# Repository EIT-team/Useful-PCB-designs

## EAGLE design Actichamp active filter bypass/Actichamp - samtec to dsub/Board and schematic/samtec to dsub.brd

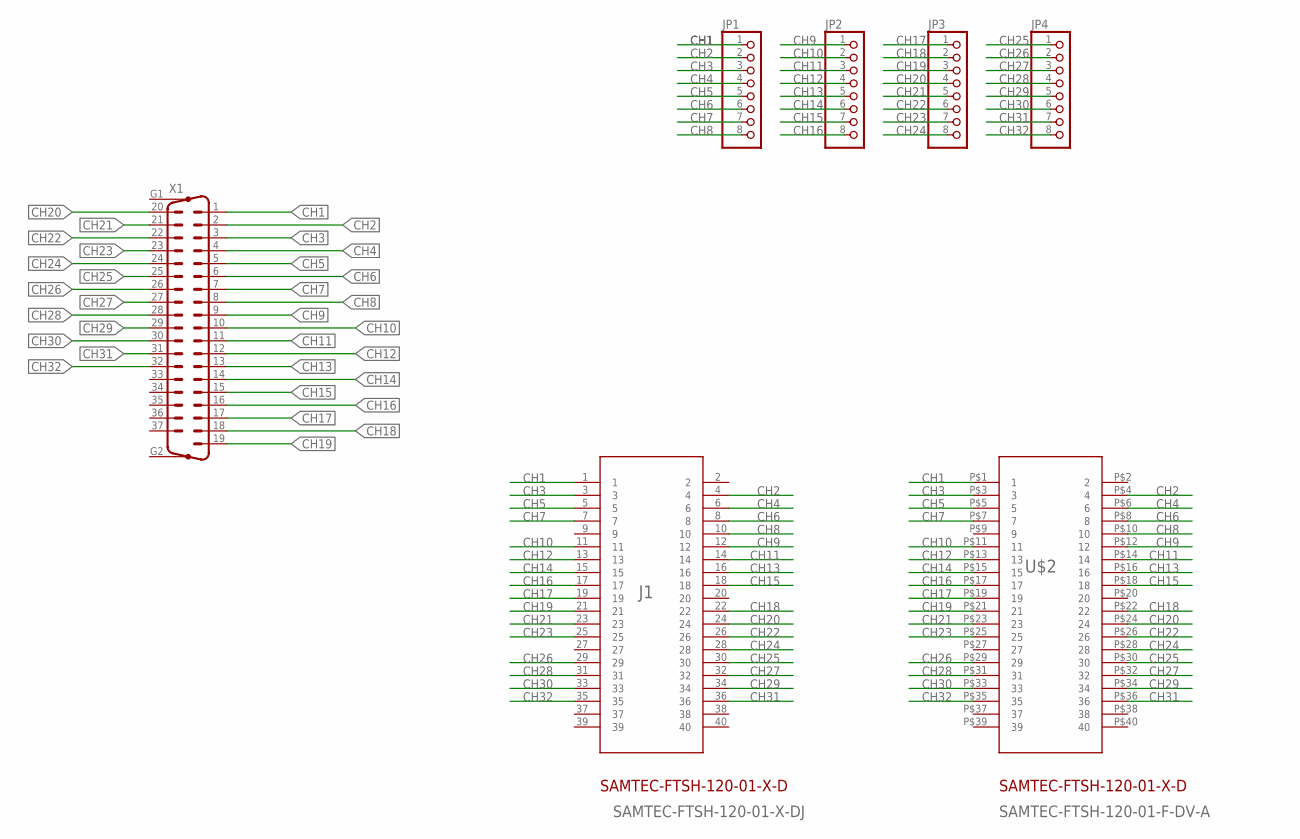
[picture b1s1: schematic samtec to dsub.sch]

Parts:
J1: SAMTEC-FTSH-120-01-X-DJ; SAMTEC-FTSH-120-01-X-D
JP1, JP2, JP3, JP4: PINHD-1X8; 1X08
U$2: SAMTEC-FTSH-120-01-F-DV-A; SAMTEC-FTSH-LARGEPAD
X1: M37HP

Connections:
CH1: J1.1, JP1.1, U$2.P$1 (1), X1.1
CH2: J1.4, JP1.2, U$2.P$4 (4), X1.2
CH3: J1.3, JP1.3, U$2.P$3 (3), X1.3
CH4: J1.6, JP1.4, U$2.P$6 (6), X1.4
CH5: J1.5, JP1.5, U$2.P$5 (5), X1.5
CH6: J1.8, JP1.6, U$2.P$8 (8), X1.6
CH7: J1.7, JP1.7, U$2.P$7 (7), X1.7
CH8: J1.10, JP1.8, U$2.P$10 (10), X1.8
CH9: J1.12, JP2.1, U$2.P$12 (12), X1.9
CH10: J1.11, JP2.2, U$2.P$11 (11), X1.10
CH11: J1.14, JP2.3, U$2.P$14 (14), X1.11
CH12: J1.13, JP2.4, U$2.P$13 (13), X1.12
CH13: J1.16, JP2.5, U$2.P$16 (16), X1.13
CH14: J1.15, JP2.6, U$2.P$15 (15), X1.14
CH15: J1.18, JP2.7, U$2.P$18 (18), X1.15
CH16: J1.17, JP2.8, U$2.P$17 (17), X1.16
CH17: J1.19, JP3.1, U$2.P$19 (19), X1.17
CH18: J1.22, JP3.2, U$2.P$22 (22), X1.18
CH19: J1.21, JP3.3, U$2.P$21 (21), X1.19
CH20: J1.24, JP3.4, U$2.P$24 (24), X1.20
CH21: J1.23, JP3.5, U$2.P$23 (23), X1.21
CH22: J1.26, JP3.6, U$2.P$26 (26), X1.22
CH23: J1.25, JP3.7, U$2.P$25 (25), X1.23
CH24: J1.28, JP3.8, U$2.P$28 (28), X1.24
CH25: J1.30, JP4.1, U$2.P$30 (30), X1.25
CH26: J1.29, JP4.2, U$2.P$29 (29), X1.26
CH27: J1.32, JP4.3, U$2.P$32 (32), X1.27
CH28: J1.31, JP4.4, U$2.P$31 (31), X1.28
CH29: J1.34, JP4.5, U$2.P$34 (34), X1.29
CH30: J1.33, JP4.6, U$2.P$33 (33), X1.30
CH31: J1.36, JP4.7, U$2.P$36 (36), X1.31
CH32: J1.35, JP4.8, U$2.P$35 (35), X1.32

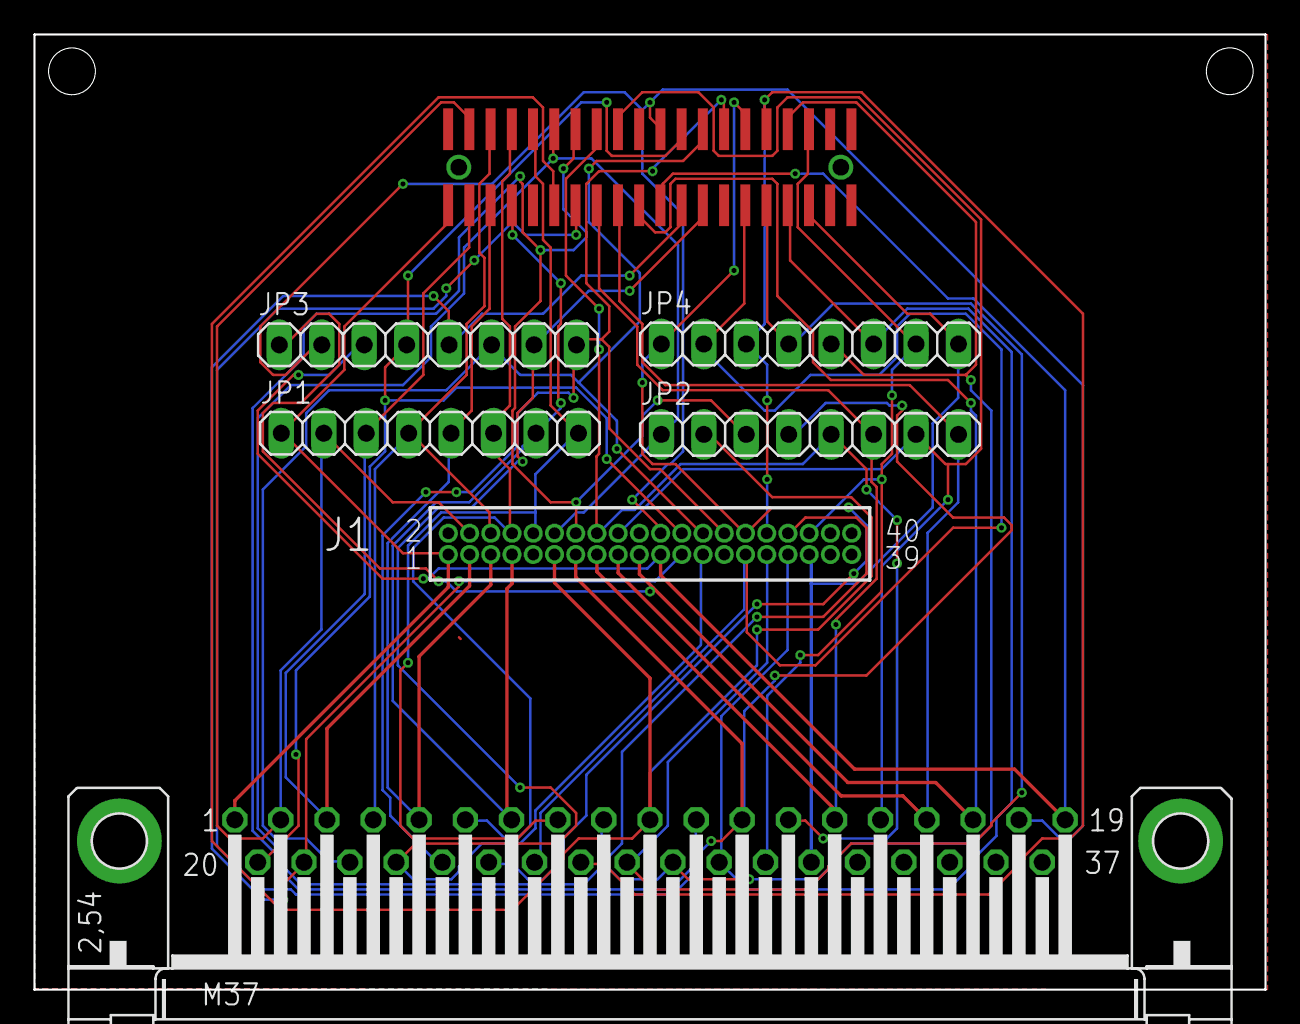
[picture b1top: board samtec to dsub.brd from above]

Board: 2 copper layers, 73.7 x 57.1 mm, 7 parts (0 on the bottom side), 32 nets.

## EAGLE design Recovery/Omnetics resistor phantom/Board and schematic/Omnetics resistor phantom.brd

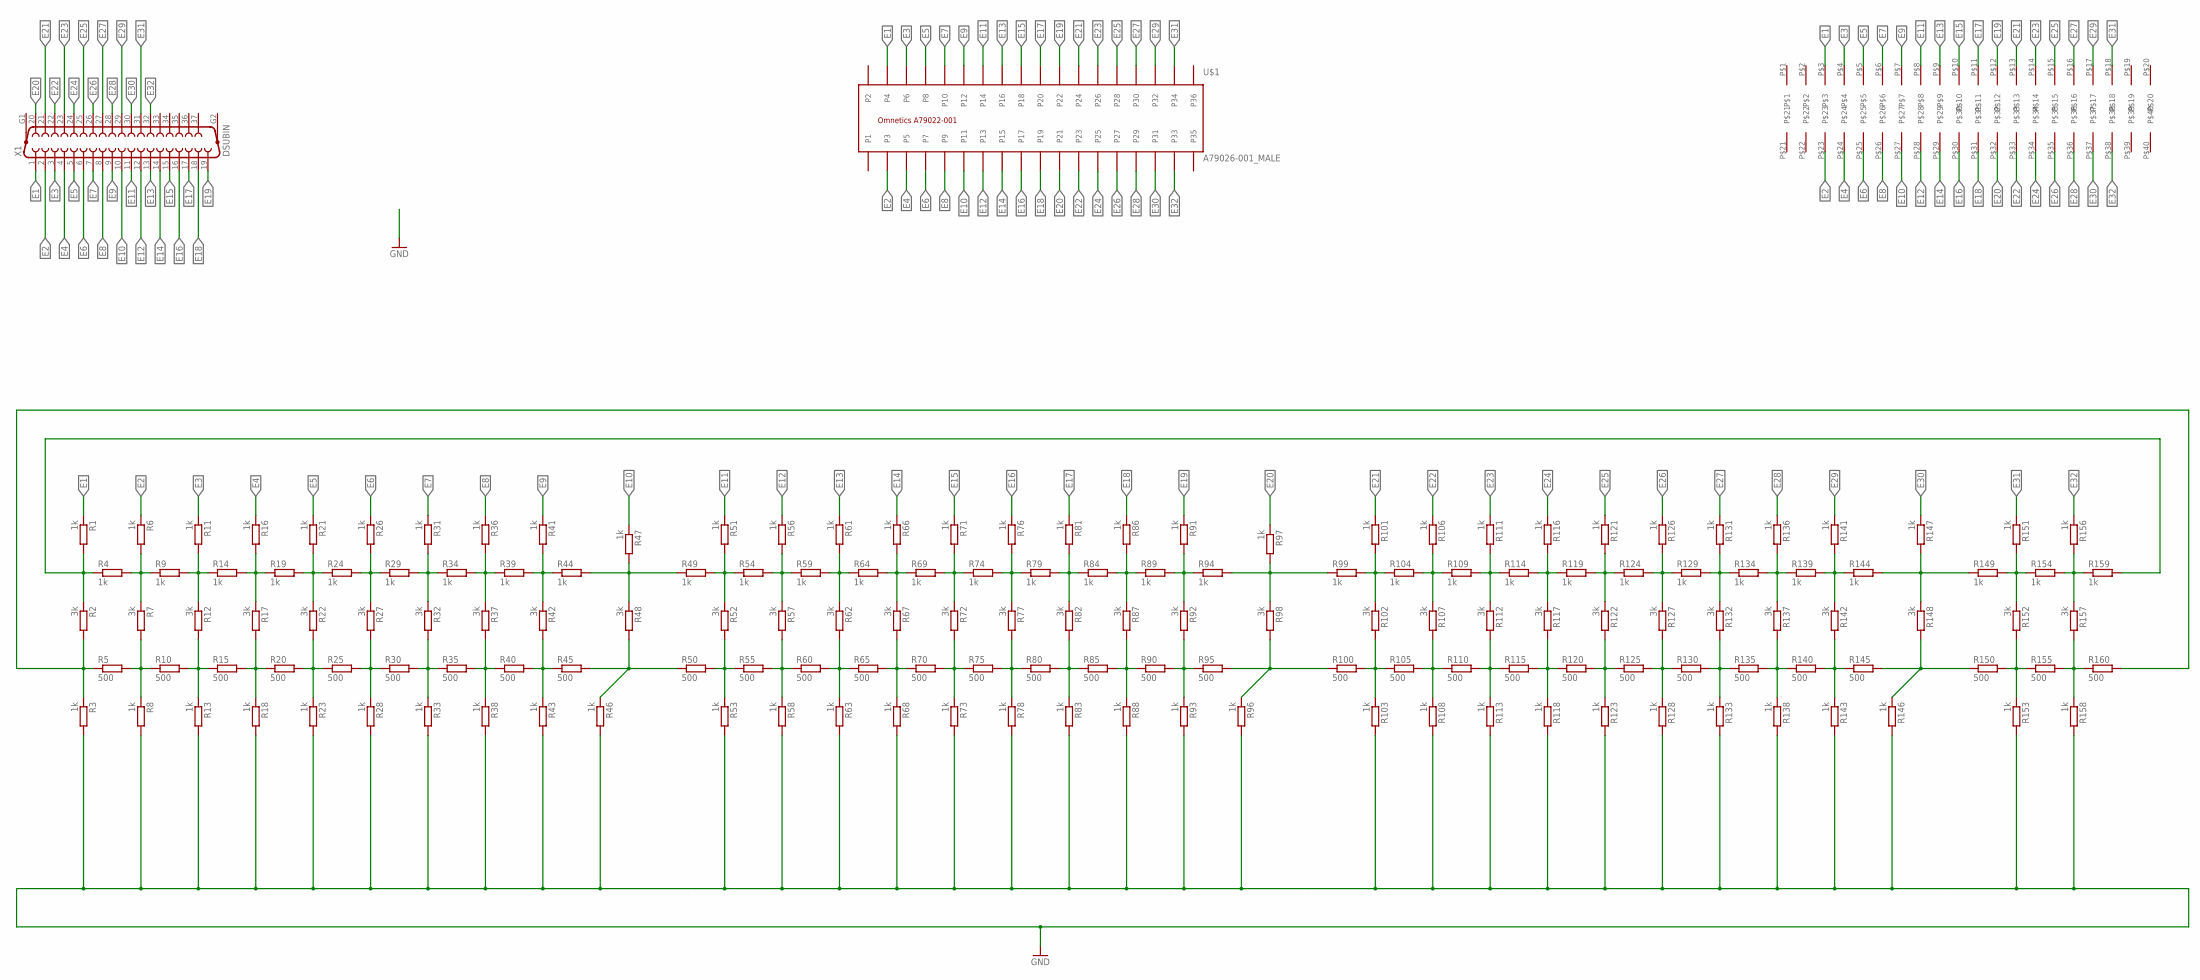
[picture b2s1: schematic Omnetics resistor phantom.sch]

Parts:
R1, R3, R4, R6, R8, R9, R11, R13, R14, R16, R18, R19, R21, R23, R24, R26, R28, R29, R31, R33, R34, R36, R38, R39, R41, R43, R44, R46, R47, R49, R51, R53, R54, R56, R58, R59, R61, R63, R64, R66, R68, R69, R71, R73, R74, R76, R78, R79, R81, R83, R84, R86, R88, R89, R91, R93, R94, R96, R97, R99, R101, R103, R104, R106, R108, R109, R111, R113, R114, R116, R118, R119, R121, R123, R124, R126, R128, R129, R131, R133, R134, R136, R138, R139, R141, R143, R144, R146, R147, R149, R151, R153, R154, R156, R158, R159: 1k; R0402
R2, R7, R12, R17, R22, R27, R32, R37, R42, R48, R52, R57, R62, R67, R72, R77, R82, R87, R92, R98, R102, R107, R112, R117, R122, R127, R132, R137, R142, R148, R152, R157: 3k; R0402
R5, R10, R15, R20, R25, R30, R35, R40, R45, R50, R55, R60, R65, R70, R75, R80, R85, R90, R95, R100, R105, R110, R115, R120, R125, R130, R135, R140, R145, R150, R155, R160: 500; R0402
U$1: A79026-001_MALE
U$2: SAMTEC_FTSH_LARGEPAD; SAMTEC-FTSH-LARGEPAD
X1: DSUBIN; F37VP

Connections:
E1: R1.1, U$1.P4, U$2.P$3, X1.1
E2: R6.1, U$1.P3, U$2.P$23, X1.2
E3: R11.1, U$1.P6, U$2.P$4, X1.3
E4: R16.1, U$1.P5, U$2.P$24, X1.4
E5: R21.1, U$1.P8, U$2.P$5, X1.5
E6: R26.1, U$1.P7, U$2.P$25, X1.6
E7: R31.1, U$1.P10, U$2.P$6, X1.7
E8: R36.1, U$1.P9, U$2.P$26, X1.8
E9: R41.1, U$1.P12, U$2.P$7, X1.9
E10: R47.1, U$1.P11, U$2.P$27, X1.10
E11: R51.1, U$1.P14, U$2.P$8, X1.11
E12: R56.1, U$1.P13, U$2.P$28, X1.12
E13: R61.1, U$1.P16, U$2.P$9, X1.13
E14: R66.1, U$1.P15, U$2.P$29, X1.14
E15: R71.1, U$1.P18, U$2.P$10, X1.15
E16: R76.1, U$1.P17, U$2.P$30, X1.16
E17: R81.1, U$1.P20, U$2.P$11, X1.17
E18: R86.1, U$1.P19, U$2.P$31, X1.18
E19: R91.1, U$1.P22, U$2.P$12, X1.19
E20: R97.1, U$1.P21, U$2.P$32, X1.20
E21: R101.1, U$1.P24, U$2.P$13, X1.21
E22: R106.1, U$1.P23, U$2.P$33, X1.22
E23: R111.1, U$1.P26, U$2.P$14, X1.23
E24: R116.1, U$1.P25, U$2.P$34, X1.24
E25: R121.1, U$1.P28, U$2.P$15, X1.25
E26: R126.1, U$1.P27, U$2.P$35, X1.26
E27: R131.1, U$1.P30, U$2.P$16, X1.27
E28: R136.1, U$1.P29, U$2.P$36, X1.28
E29: R141.1, U$1.P32, U$2.P$17, X1.29
E30: R147.1, U$1.P31, U$2.P$37, X1.30
E31: R151.1, U$1.P34, U$2.P$18, X1.31
E32: R156.1, U$1.P33, U$2.P$38, X1.32
E38: R1.2, R2.1, R4.1, R159.2
E39: R4.2, R6.2, R7.1, R9.1
E40: R9.2, R11.2, R12.1, R14.1
E41: R14.2, R16.2, R17.1, R19.1
E42: R19.2, R21.2, R22.1, R24.1
E43: R24.2, R26.2, R27.1, R29.1
E44: R29.2, R31.2, R32.1, R34.1
E45: R34.2, R36.2, R37.1, R39.1
E46: R39.2, R41.2, R42.1, R44.1
E47: R44.2, R47.2, R48.1, R49.1
E48: R49.2, R51.2, R52.1, R54.1
E49: R54.2, R56.2, R57.1, R59.1
E50: R59.2, R61.2, R62.1, R64.1
E51: R64.2, R66.2, R67.1, R69.1
E52: R69.2, R71.2, R72.1, R74.1
E53: R74.2, R76.2, R77.1, R79.1
E54: R79.2, R81.2, R82.1, R84.1
E55: R84.2, R86.2, R87.1, R89.1
E56: R89.2, R91.2, R92.1, R94.1
E57: R94.2, R97.2, R98.1, R99.1
E58: R99.2, R101.2, R102.1, R104.1
E59: R104.2, R106.2, R107.1, R109.1
E60: R109.2, R111.2, R112.1, R114.1
E61: R114.2, R116.2, R117.1, R119.1
E63: R124.2, R126.2, R127.1, R129.1
E64: R129.2, R131.2, R132.1, R134.1
E65: R134.2, R136.2, R137.1, R139.1
E66: R139.2, R141.2, R142.1, R144.1
E67: R144.2, R147.2, R148.1, R149.1
E68: R149.2, R151.2, R152.1, R154.1
E69: R154.2, R156.2, R157.1, R159.1
GND: R3.2, R8.2, R13.2, R18.2, R23.2, R28.2, R33.2, R38.2, R43.2, R46.2, R53.2, R58.2, R63.2, R68.2, R73.2, R78.2, R83.2, R88.2, R93.2, R96.2, R103.2, R108.2, R113.2, R118.2, R123.2, R128.2, R133.2, R138.2, R143.2, R146.2, R153.2, R158.2
unnamed: R119.2, R121.2, R122.1, R124.1
unnamed: R2.2, R3.1, R5.1, R160.2
unnamed: R5.2, R7.2, R8.1, R10.1
unnamed: R10.2, R12.2, R13.1, R15.1
unnamed: R15.2, R17.2, R18.1, R20.1
unnamed: R20.2, R22.2, R23.1, R25.1
unnamed: R25.2, R27.2, R28.1, R30.1
unnamed: R30.2, R32.2, R33.1, R35.1
unnamed: R35.2, R37.2, R38.1, R40.1
unnamed: R40.2, R42.2, R43.1, R45.1
unnamed: R50.2, R52.2, R53.1, R55.1
unnamed: R55.2, R57.2, R58.1, R60.1
unnamed: R60.2, R62.2, R63.1, R65.1
unnamed: R65.2, R67.2, R68.1, R70.1
unnamed: R70.2, R72.2, R73.1, R75.1
unnamed: R75.2, R77.2, R78.1, R80.1
unnamed: R80.2, R82.2, R83.1, R85.1
unnamed: R85.2, R87.2, R88.1, R90.1
unnamed: R90.2, R92.2, R93.1, R95.1
unnamed: R100.2, R102.2, R103.1, R105.1
unnamed: R105.2, R107.2, R108.1, R110.1
unnamed: R110.2, R112.2, R113.1, R115.1
unnamed: R115.2, R117.2, R118.1, R120.1
unnamed: R120.2, R122.2, R123.1, R125.1
unnamed: R125.2, R127.2, R128.1, R130.1
unnamed: R130.2, R132.2, R133.1, R135.1
unnamed: R135.2, R137.2, R138.1, R140.1
unnamed: R140.2, R142.2, R143.1, R145.1
unnamed: R150.2, R152.2, R153.1, R155.1
unnamed: R155.2, R157.2, R158.1, R160.1
SW_IN1: R45.2, R46.1, R48.2, R50.1
SW_IN2: R95.2, R96.1, R98.2, R100.1
SW_IN3: R145.2, R146.1, R148.2, R150.1

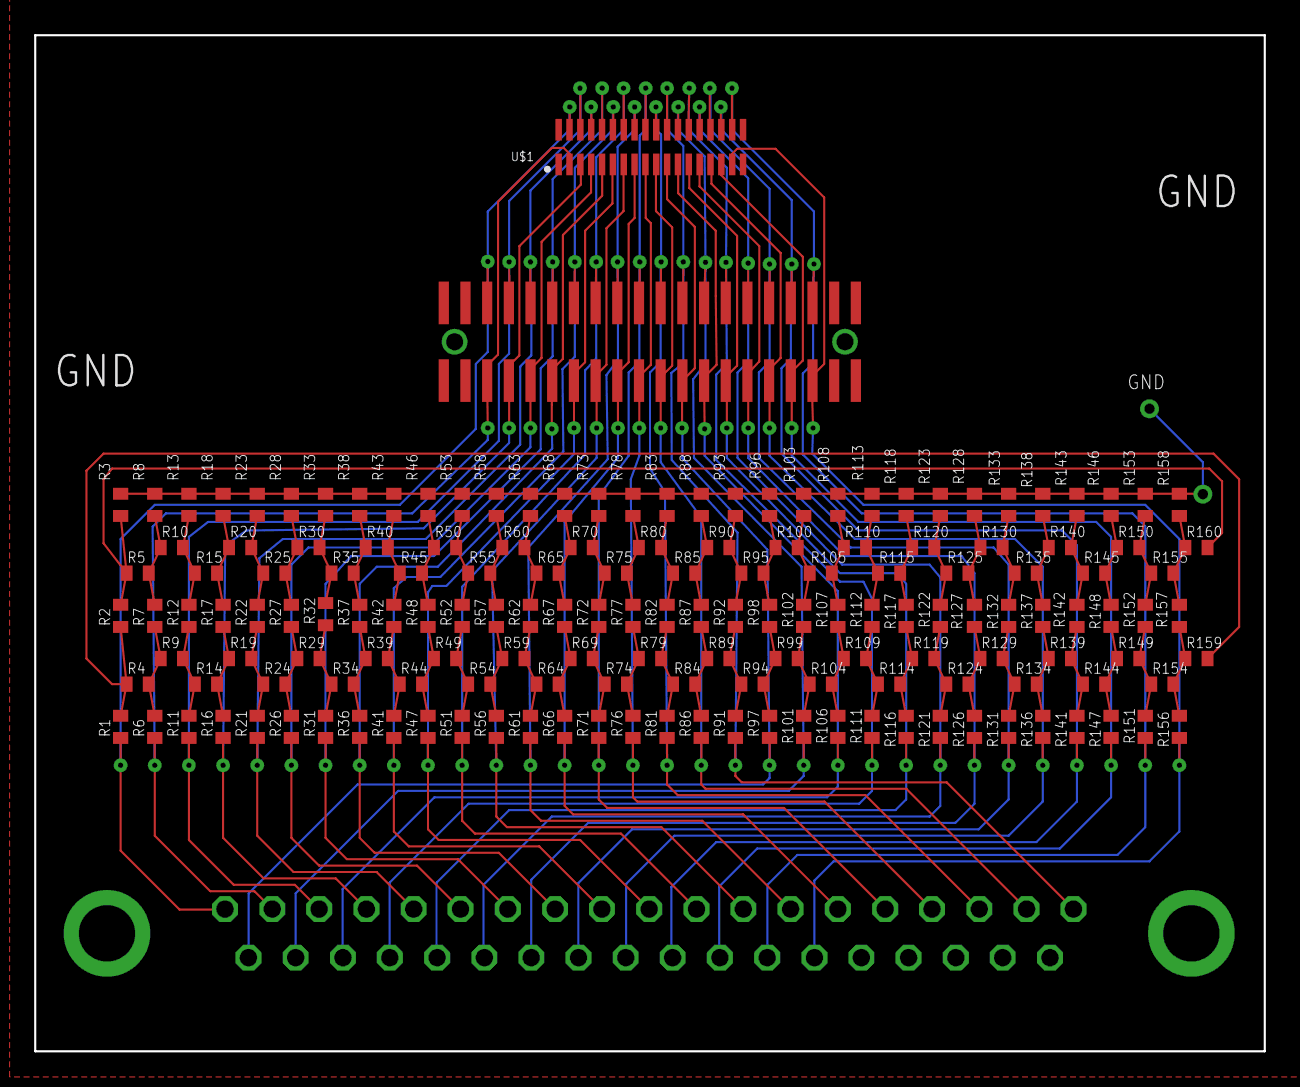
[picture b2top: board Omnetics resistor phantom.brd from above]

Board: 2 copper layers, 72.0 x 59.5 mm, 163 parts (1 on the bottom side), 97 nets.

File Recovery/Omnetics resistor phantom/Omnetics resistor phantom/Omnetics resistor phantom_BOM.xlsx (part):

Part | Value | Device | Package | Description | MPN | OC_FARNELL | PCBTRAINFREE
R1 | 1k | R-EU_R0402 | R0402 | RESISTOR, European symbol | MC00625W040211K | 1358043 | PCBTRAINFREESTOCK
R2 | 3k | R-EU_R0402 | R0402 | RESISTOR, European symbol | MC00625W040213K | 2130389 | PCBTRAINFREESTOCK
R3 | 1k | R-EU_R0402 | R0402 | RESISTOR, European symbol | MC00625W040211K | 1358043 | PCBTRAINFREESTOCK
R4 | 1k | R-EU_R0402 | R0402 | RESISTOR, European symbol | MC00625W040211K | 1358043 | PCBTRAINFREESTOCK
R5 | 500 | R-EU_R0402 | R0402 | RESISTOR, European symbol | MC00625W04021510R | 2130329 | PCBTRAINFREESTOCK
R6 | 1k | R-EU_R0402 | R0402 | RESISTOR, European symbol | MC00625W040211K | 1358043 | PCBTRAINFREESTOCK
R7 | 3k | R-EU_R0402 | R0402 | RESISTOR, European symbol | MC00625W040213K | 2130389 | PCBTRAINFREESTOCK
R8 | 1k | R-EU_R0402 | R0402 | RESISTOR, European symbol | MC00625W040211K | 1358043 | PCBTRAINFREESTOCK
R9 | 1k | R-EU_R0402 | R0402 | RESISTOR, European symbol | MC00625W040211K | 1358043 | PCBTRAINFREESTOCK
R10 | 500 | R-EU_R0402 | R0402 | RESISTOR, European symbol | MC00625W04021510R | 2130329 | PCBTRAINFREESTOCK
R11 | 1k | R-EU_R0402 | R0402 | RESISTOR, European symbol | MC00625W040211K | 1358043 | PCBTRAINFREESTOCK
R12 | 3k | R-EU_R0402 | R0402 | RESISTOR, European symbol | MC00625W040213K | 2130389 | PCBTRAINFREESTOCK
R13 | 1k | R-EU_R0402 | R0402 | RESISTOR, European symbol | MC00625W040211K | 1358043 | PCBTRAINFREESTOCK
R14 | 1k | R-EU_R0402 | R0402 | RESISTOR, European symbol | MC00625W040211K | 1358043 | PCBTRAINFREESTOCK
R15 | 500 | R-EU_R0402 | R0402 | RESISTOR, European symbol | MC00625W04021510R | 2130329 | PCBTRAINFREESTOCK
R16 | 1k | R-EU_R0402 | R0402 | RESISTOR, European symbol | MC00625W040211K | 1358043 | PCBTRAINFREESTOCK
R17 | 3k | R-EU_R0402 | R0402 | RESISTOR, European symbol | MC00625W040213K | 2130389 | PCBTRAINFREESTOCK
R18 | 1k | R-EU_R0402 | R0402 | RESISTOR, European symbol | MC00625W040211K | 1358043 | PCBTRAINFREESTOCK
R19 | 1k | R-EU_R0402 | R0402 | RESISTOR, European symbol | MC00625W040211K | 1358043 | PCBTRAINFREESTOCK
R20 | 500 | R-EU_R0402 | R0402 | RESISTOR, European symbol | MC00625W04021510R | 2130329 | PCBTRAINFREESTOCK
R21 | 1k | R-EU_R0402 | R0402 | RESISTOR, European symbol | MC00625W040211K | 1358043 | PCBTRAINFREESTOCK
R22 | 3k | R-EU_R0402 | R0402 | RESISTOR, European symbol | MC00625W040213K | 2130389 | PCBTRAINFREESTOCK
R23 | 1k | R-EU_R0402 | R0402 | RESISTOR, European symbol | MC00625W040211K | 1358043 | PCBTRAINFREESTOCK
R24 | 1k | R-EU_R0402 | R0402 | RESISTOR, European symbol | MC00625W040211K | 1358043 | PCBTRAINFREESTOCK
R25 | 500 | R-EU_R0402 | R0402 | RESISTOR, European symbol | MC00625W04021510R | 2130329 | PCBTRAINFREESTOCK
R26 | 1k | R-EU_R0402 | R0402 | RESISTOR, European symbol | MC00625W040211K | 1358043 | PCBTRAINFREESTOCK
R27 | 3k | R-EU_R0402 | R0402 | RESISTOR, European symbol | MC00625W040213K | 2130389 | PCBTRAINFREESTOCK
R28 | 1k | R-EU_R0402 | R0402 | RESISTOR, European symbol | MC00625W040211K | 1358043 | PCBTRAINFREESTOCK
R29 | 1k | R-EU_R0402 | R0402 | RESISTOR, European symbol | MC00625W040211K | 1358043 | PCBTRAINFREESTOCK
R30 | 500 | R-EU_R0402 | R0402 | RESISTOR, European symbol | MC00625W04021510R | 2130329 | PCBTRAINFREESTOCK
R31 | 1k | R-EU_R0402 | R0402 | RESISTOR, European symbol | MC00625W040211K | 1358043 | PCBTRAINFREESTOCK
R32 | 3k | R-EU_R0402 | R0402 | RESISTOR, European symbol | MC00625W040213K | 2130389 | PCBTRAINFREESTOCK
R33 | 1k | R-EU_R0402 | R0402 | RESISTOR, European symbol | MC00625W040211K | 1358043 | PCBTRAINFREESTOCK
R34 | 1k | R-EU_R0402 | R0402 | RESISTOR, European symbol | MC00625W040211K | 1358043 | PCBTRAINFREESTOCK
R35 | 500 | R-EU_R0402 | R0402 | RESISTOR, European symbol | MC00625W04021510R | 2130329 | PCBTRAINFREESTOCK
R36 | 1k | R-EU_R0402 | R0402 | RESISTOR, European symbol | MC00625W040211K | 1358043 | PCBTRAINFREESTOCK
R37 | 3k | R-EU_R0402 | R0402 | RESISTOR, European symbol | MC00625W040213K | 2130389 | PCBTRAINFREESTOCK
R38 | 1k | R-EU_R0402 | R0402 | RESISTOR, European symbol | MC00625W040211K | 1358043 | PCBTRAINFREESTOCK
R39 | 1k | R-EU_R0402 | R0402 | RESISTOR, European symbol | MC00625W040211K | 1358043 | PCBTRAINFREESTOCK
R40 | 500 | R-EU_R0402 | R0402 | RESISTOR, European symbol | MC00625W04021510R | 2130329 | PCBTRAINFREESTOCK
R41 | 1k | R-EU_R0402 | R0402 | RESISTOR, European symbol | MC00625W040211K | 1358043 | PCBTRAINFREESTOCK
R42 | 3k | R-EU_R0402 | R0402 | RESISTOR, European symbol | MC00625W040213K | 2130389 | PCBTRAINFREESTOCK
R43 | 1k | R-EU_R0402 | R0402 | RESISTOR, European symbol | MC00625W040211K | 1358043 | PCBTRAINFREESTOCK
R44 | 1k | R-EU_R0402 | R0402 | RESISTOR, European symbol | MC00625W040211K | 1358043 | PCBTRAINFREESTOCK
R45 | 500 | R-EU_R0402 | R0402 | RESISTOR, European symbol | MC00625W04021510R | 2130329 | PCBTRAINFREESTOCK
R46 | 1k | R-EU_R0402 | R0402 | RESISTOR, European symbol | MC00625W040211K | 1358043 | PCBTRAINFREESTOCK
R47 | 1k | R-EU_R0402 | R0402 | RESISTOR, European symbol | MC00625W040211K | 1358043 | PCBTRAINFREESTOCK
R48 | 3k | R-EU_R0402 | R0402 | RESISTOR, European symbol | MC00625W040213K | 2130389 | PCBTRAINFREESTOCK
R49 | 1k | R-EU_R0402 | R0402 | RESISTOR, European symbol | MC00625W040211K | 1358043 | PCBTRAINFREESTOCK
R50 | 500 | R-EU_R0402 | R0402 | RESISTOR, European symbol | MC00625W04021510R | 2130329 | PCBTRAINFREESTOCK
R51 | 1k | R-EU_R0402 | R0402 | RESISTOR, European symbol | MC00625W040211K | 1358043 | PCBTRAINFREESTOCK
R52 | 3k | R-EU_R0402 | R0402 | RESISTOR, European symbol | MC00625W040213K | 2130389 | PCBTRAINFREESTOCK
R53 | 1k | R-EU_R0402 | R0402 | RESISTOR, European symbol | MC00625W040211K | 1358043 | PCBTRAINFREESTOCK
R54 | 1k | R-EU_R0402 | R0402 | RESISTOR, European symbol | MC00625W040211K | 1358043 | PCBTRAINFREESTOCK
R55 | 500 | R-EU_R0402 | R0402 | RESISTOR, European symbol | MC00625W04021510R | 2130329 | PCBTRAINFREESTOCK
R56 | 1k | R-EU_R0402 | R0402 | RESISTOR, European symbol | MC00625W040211K | 1358043 | PCBTRAINFREESTOCK
R57 | 3k | R-EU_R0402 | R0402 | RESISTOR, European symbol | MC00625W040213K | 2130389 | PCBTRAINFREESTOCK
R58 | 1k | R-EU_R0402 | R0402 | RESISTOR, European symbol | MC00625W040211K | 1358043 | PCBTRAINFREESTOCK
R59 | 1k | R-EU_R0402 | R0402 | RESISTOR, European symbol | MC00625W040211K | 1358043 | PCBTRAINFREESTOCK
R60 | 500 | R-EU_R0402 | R0402 | RESISTOR, European symbol | MC00625W04021510R | 2130329 | PCBTRAINFREESTOCK
R61 | 1k | R-EU_R0402 | R0402 | RESISTOR, European symbol | MC00625W040211K | 1358043 | PCBTRAINFREESTOCK
R62 | 3k | R-EU_R0402 | R0402 | RESISTOR, European symbol | MC00625W040213K | 2130389 | PCBTRAINFREESTOCK
R63 | 1k | R-EU_R0402 | R0402 | RESISTOR, European symbol | MC00625W040211K | 1358043 | PCBTRAINFREESTOCK
R64 | 1k | R-EU_R0402 | R0402 | RESISTOR, European symbol | MC00625W040211K | 1358043 | PCBTRAINFREESTOCK
R65 | 500 | R-EU_R0402 | R0402 | RESISTOR, European symbol | MC00625W04021510R | 2130329 | PCBTRAINFREESTOCK
R66 | 1k | R-EU_R0402 | R0402 | RESISTOR, European symbol | MC00625W040211K | 1358043 | PCBTRAINFREESTOCK
R67 | 3k | R-EU_R0402 | R0402 | RESISTOR, European symbol | MC00625W040213K | 2130389 | PCBTRAINFREESTOCK
R68 | 1k | R-EU_R0402 | R0402 | RESISTOR, European symbol | MC00625W040211K | 1358043 | PCBTRAINFREESTOCK
R69 | 1k | R-EU_R0402 | R0402 | RESISTOR, European symbol | MC00625W040211K | 1358043 | PCBTRAINFREESTOCK
R70 | 500 | R-EU_R0402 | R0402 | RESISTOR, European symbol | MC00625W04021510R | 2130329 | PCBTRAINFREESTOCK
R71 | 1k | R-EU_R0402 | R0402 | RESISTOR, European symbol | MC00625W040211K | 1358043 | PCBTRAINFREESTOCK
R72 | 3k | R-EU_R0402 | R0402 | RESISTOR, European symbol | MC00625W040213K | 2130389 | PCBTRAINFREESTOCK
R73 | 1k | R-EU_R0402 | R0402 | RESISTOR, European symbol | MC00625W040211K | 1358043 | PCBTRAINFREESTOCK
R74 | 1k | R-EU_R0402 | R0402 | RESISTOR, European symbol | MC00625W040211K | 1358043 | PCBTRAINFREESTOCK
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
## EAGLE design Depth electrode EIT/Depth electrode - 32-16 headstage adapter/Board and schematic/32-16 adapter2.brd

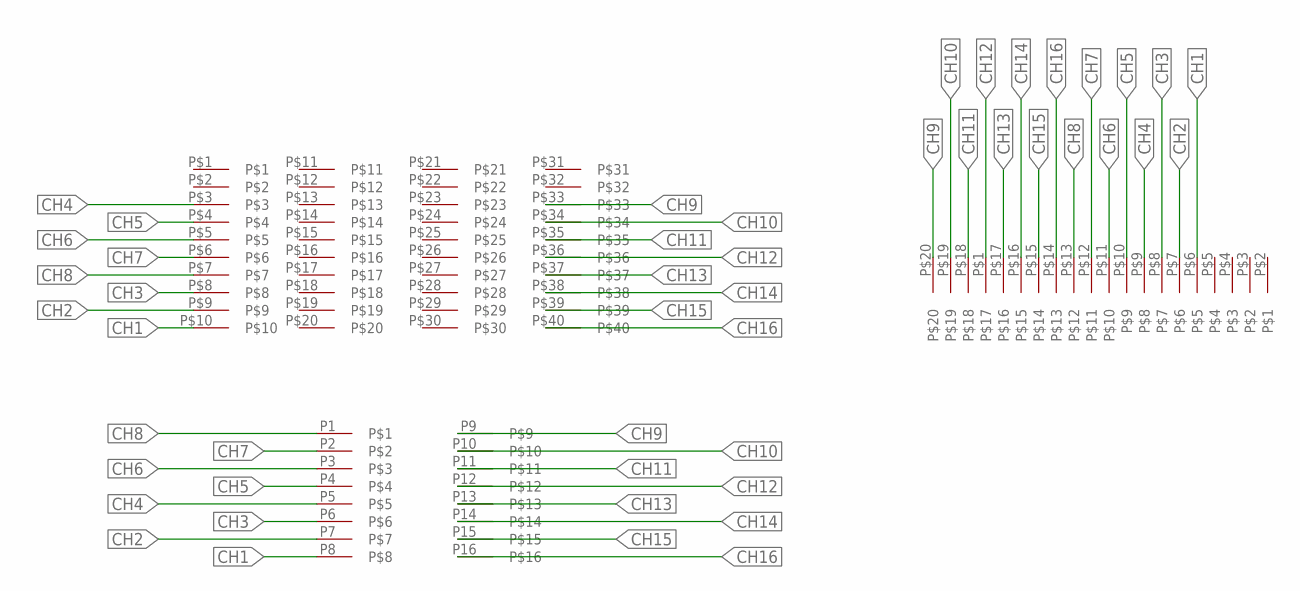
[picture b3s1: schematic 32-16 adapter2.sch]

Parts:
U$1: 16_PAD
U$2: DIL-16CHN
U$3: MOLC-SAMTEC-32

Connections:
CH1: U$1.P$6, U$2.P8, U$3.P$10
CH2: U$1.P$7, U$2.P7, U$3.P$9
CH3: U$1.P$8, U$2.P6, U$3.P$8
CH4: U$1.P$9, U$2.P5, U$3.P$3
CH5: U$1.P$10, U$2.P4, U$3.P$4
CH6: U$1.P$11, U$2.P3, U$3.P$5
CH7: U$1.P$12, U$2.P2, U$3.P$6
CH8: U$1.P$13, U$2.P1, U$3.P$7
CH9: U$1.P$20, U$2.P9, U$3.P$33
CH10: U$1.P$19, U$2.P10, U$3.P$34
CH11: U$1.P$18, U$2.P11, U$3.P$35
CH12: U$1.P$1, U$2.P12, U$3.P$36
CH13: U$1.P$17, U$2.P13, U$3.P$37
CH14: U$1.P$16, U$2.P14, U$3.P$38
CH15: U$1.P$15, U$2.P15, U$3.P$39
CH16: U$1.P$14, U$2.P16, U$3.P$40

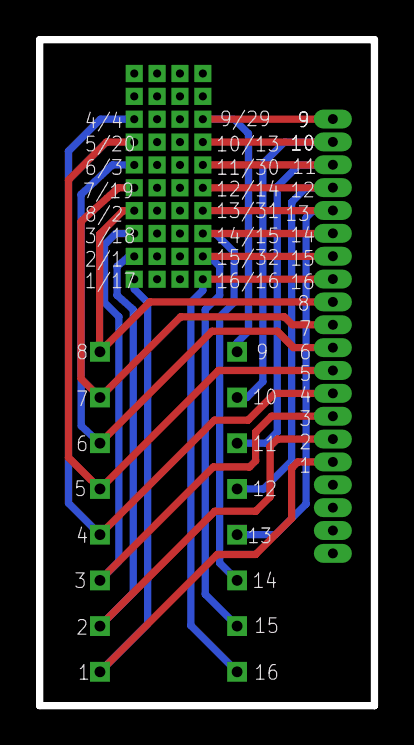
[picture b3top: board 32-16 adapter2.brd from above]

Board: 2 copper layers, 18.6 x 37.0 mm, 3 parts (0 on the bottom side), 16 nets.

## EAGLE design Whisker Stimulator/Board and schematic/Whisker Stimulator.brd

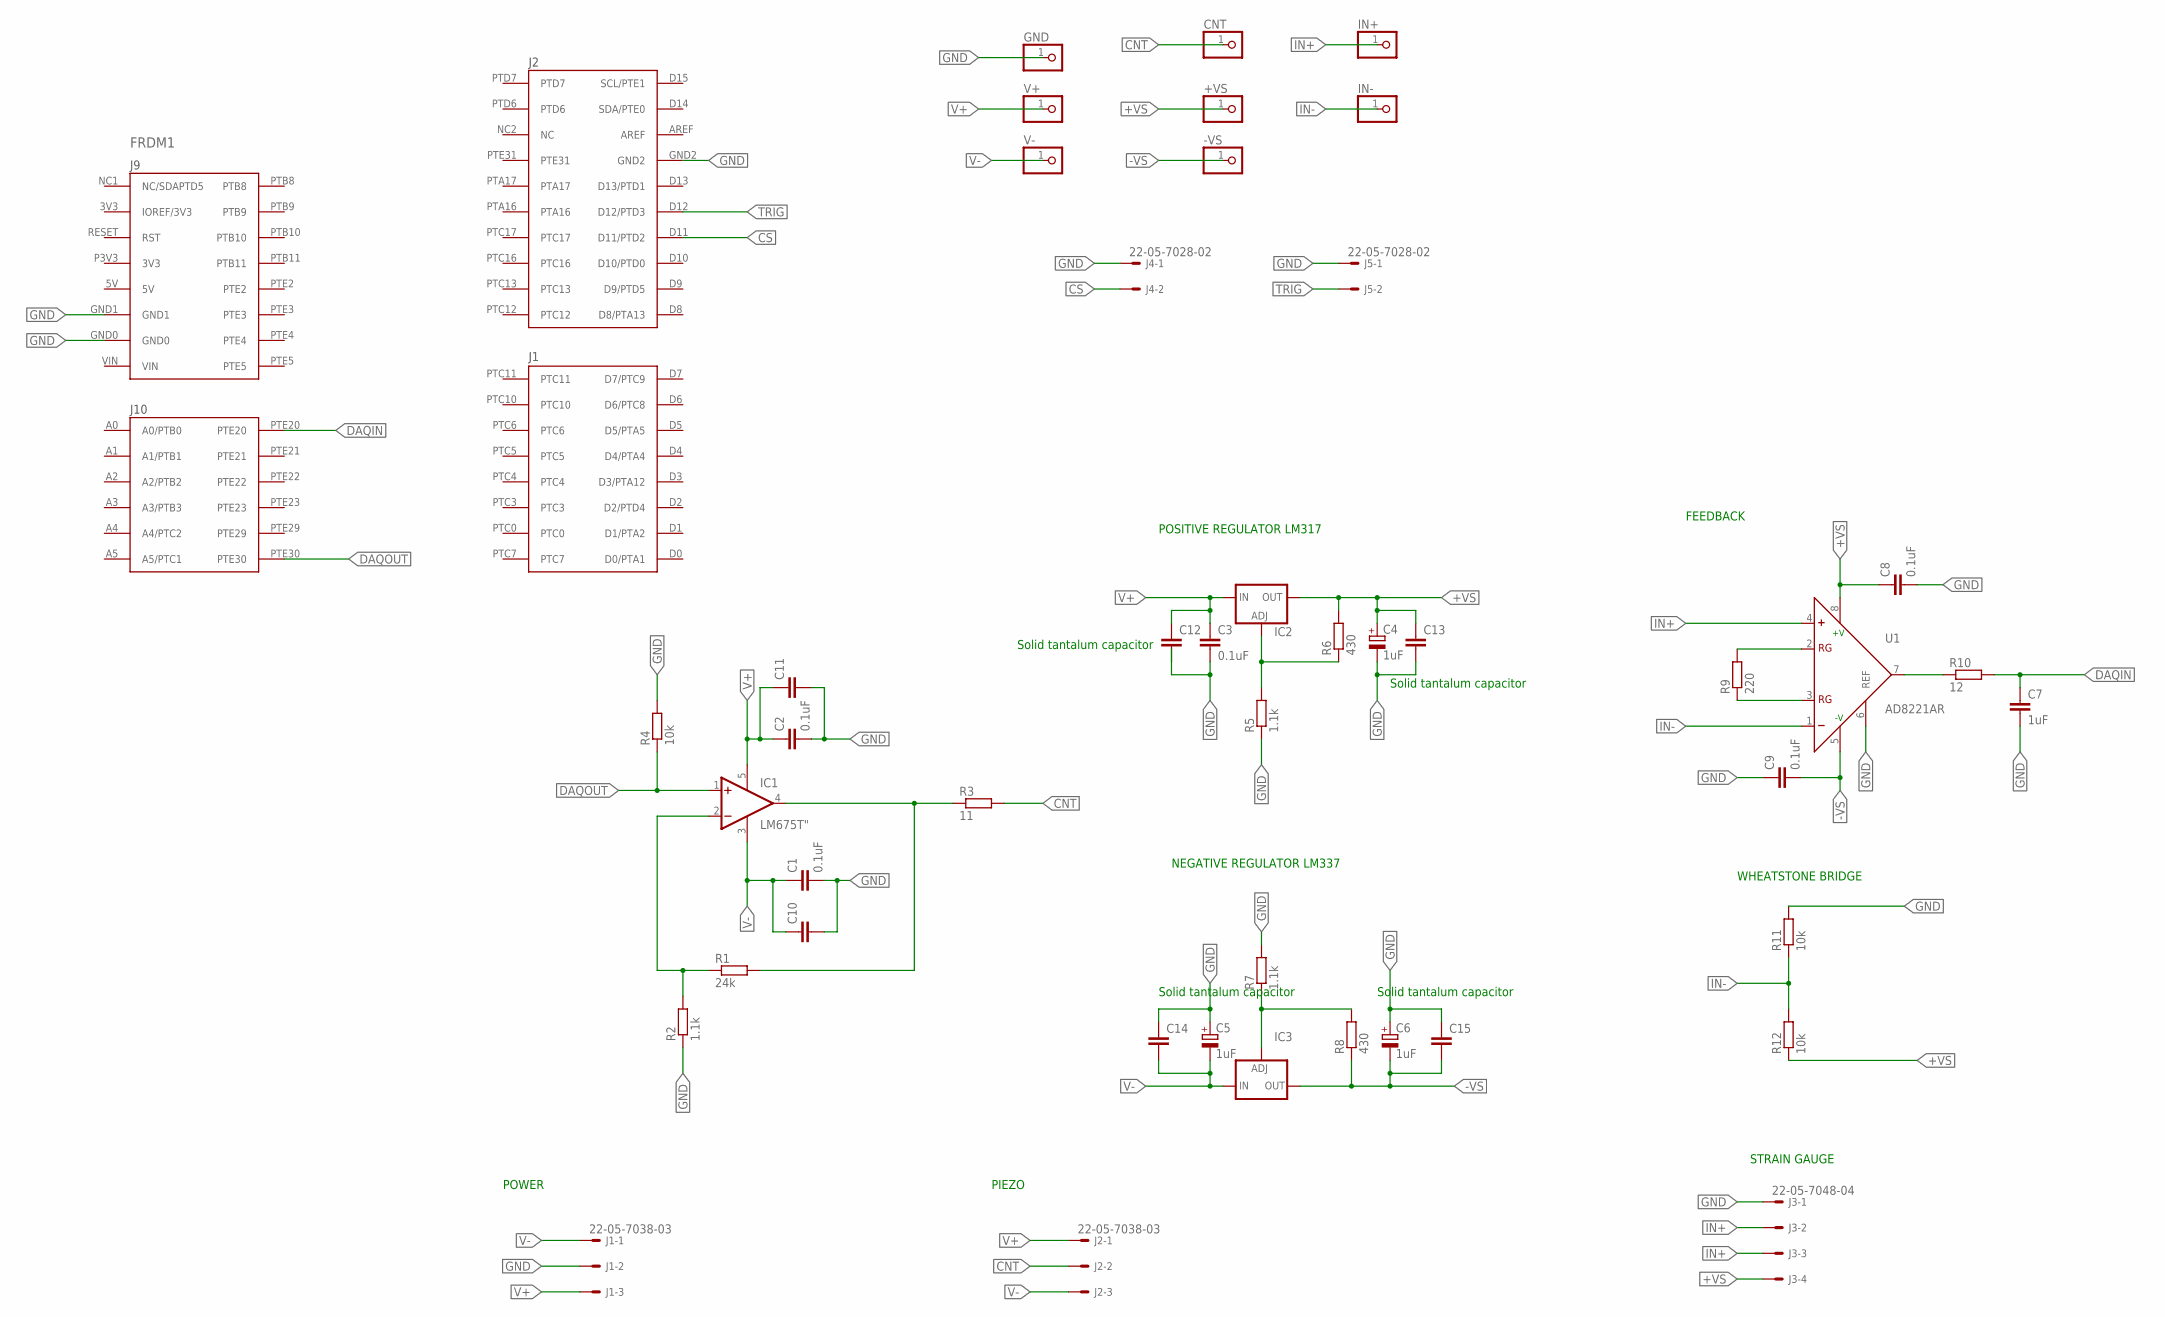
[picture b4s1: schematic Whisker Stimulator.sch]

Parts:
+VS: PINHD-1X1; 1X01
-VS: PINHD-1X1; 1X01
C1, C2, C3, C8, C9: 0.1uF; C0805
C4, C5, C6: 1uF; E2,5RE
C7: 1uF; C0805
C10, C11, C12, C13, C14, C15: 0.1uF; C050-024X044
CNT: PINHD-1X1; 1X01
FRDM1: FRDM-KL25ZNORMAL; FRDM_KL25Z_NORMAL
GND: PINHD-1X1; 1X01
IC1: LM675T"; CB360
IC2: LM317TS; 317TS
IC3: LM337TS; 337TS
IN+: PINHD-1X1; 1X01
IN-: PINHD-1X1; 1X01
J1, J2: 22-05-7038-03; 7395-03
J3: 22-05-7048-04; 7395-04
J4, J5: 22-05-7028-02; 7395-02
R1: 24k; R0805
R2, R5, R7: 1.1k; R0805
R3: 11; VMTA55
R4, R11, R12: 10k; R0805
R6, R8: 430; R0805
R9: 220; R0805
R10: 12; R0805
U1: AD8221AR; SO8
V+: PINHD-1X1; 1X01
V-: PINHD-1X1; 1X01

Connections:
+VS: +VS.1, C4.+, C8.1, C13.1, IC2.2 (OUT), J3.4, R6.2, R12.1, U1.8 (+V)
-VS: -VS.1, C6.-, C9.2, C15.2, IC3.3 (OUT), R8.1, U1.5 (-V)
CNT: CNT.1, J2.2, R3.2
CS: FRDM1.D11 (D11/PTD2), J4.2
DAQIN: C7.1, FRDM1.PTE20, R10.2
DAQOUT: FRDM1.PTE30, IC1.1 (+IN), R4.1
GND: C1.2, C2.2, C3.2, C4.-, C5.+, C6.+, C7.2, C8.2, C9.1, C10.2, C11.2, C12.2, C13.2, C14.1, C15.1, FRDM1.GND0, FRDM1.GND1, FRDM1.GND2, GND.1, J1.2, J3.1, J4.1, J5.1, R2.1, R4.2, R5.1, R7.2, R11.2, U1.6 (REF)
IN+: IN+.1, J3.2, J3.3, U1.4 (+)
IN-: IN-.1, R11.1, R12.2, U1.1 (-)
unnamed: IC2.1 (ADJ), R5.2, R6.1
unnamed: IC3.1 (ADJ), R7.1, R8.2
unnamed: IC1.4 (OUT), R1.2, R3.1
unnamed: IC1.2 (-IN), R1.1, R2.2
unnamed: R9.2, U1.2 (RG)
unnamed: R9.1, U1.3 (RG)
unnamed: R10.1, U1.7 (OUT)
TRIG: FRDM1.D12 (D12/PTD3), J5.2
V+: C2.1, C3.1, C11.1, C12.1, IC1.5 (V+), IC2.3 (IN), J1.3, J2.1, V+.1
V-: C1.1, C5.-, C10.1, C14.2, IC1.3 (V-), IC3.2 (IN), J1.1, J2.3, V-.1

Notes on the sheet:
POWER
PIEZO
POSITIVE REGULATOR LM317
NEGATIVE REGULATOR LM337
STRAIN GAUGE
FEEDBACK
WHEATSTONE BRIDGE
Solid tantalum capacitor

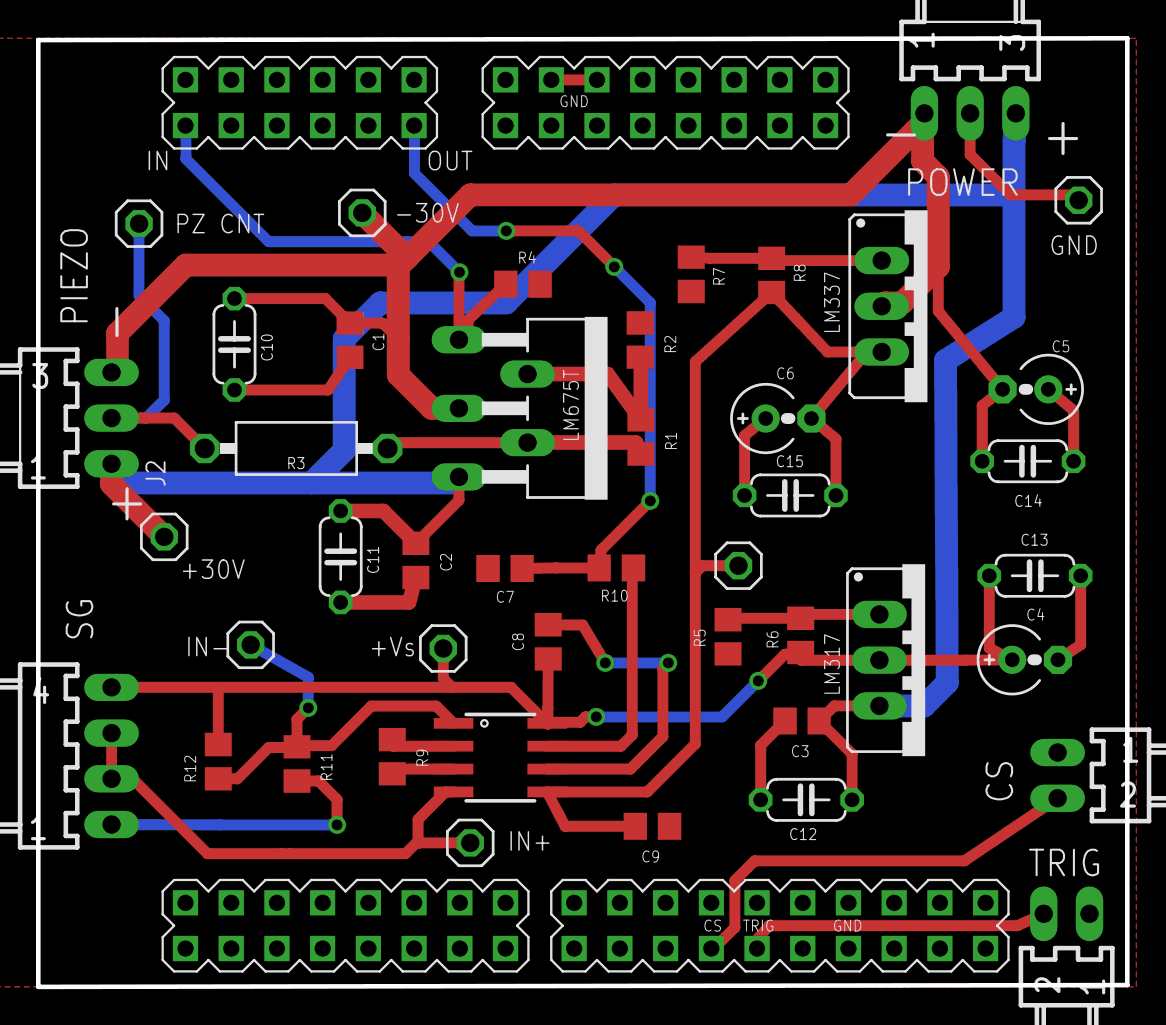
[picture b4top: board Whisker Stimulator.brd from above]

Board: 2 copper layers, 60.5 x 52.7 mm, 45 parts (0 on the bottom side), 19 nets.
